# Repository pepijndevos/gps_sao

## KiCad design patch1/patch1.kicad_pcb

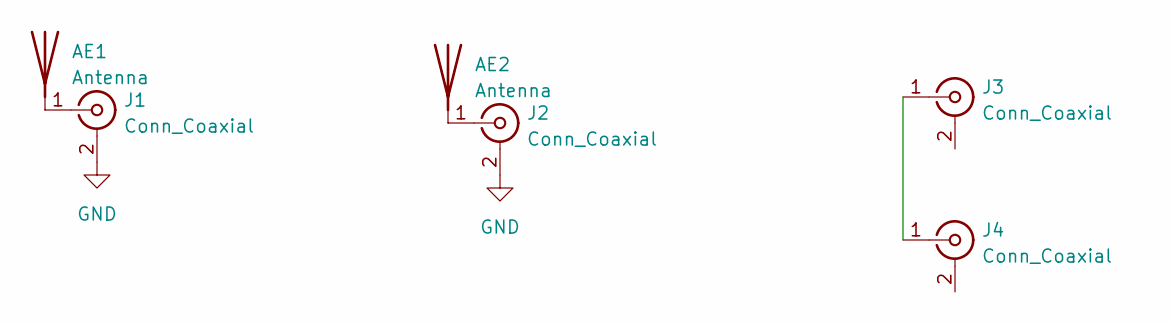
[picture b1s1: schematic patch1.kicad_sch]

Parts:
AE1: Antenna; patch_antenna_1.6ghz_cp
AE2: Antenna; patch_antenna_1.6ghz
J1, J2, J3, J4: Conn_Coaxial; coax

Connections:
GND: J1.2 (Ext), J2.2 (Ext)
unnamed: AE1.1 (A), J1.1 (In)
unnamed: AE2.1 (A), J2.1 (In)
unnamed: J3.1 (In), J4.1 (In)

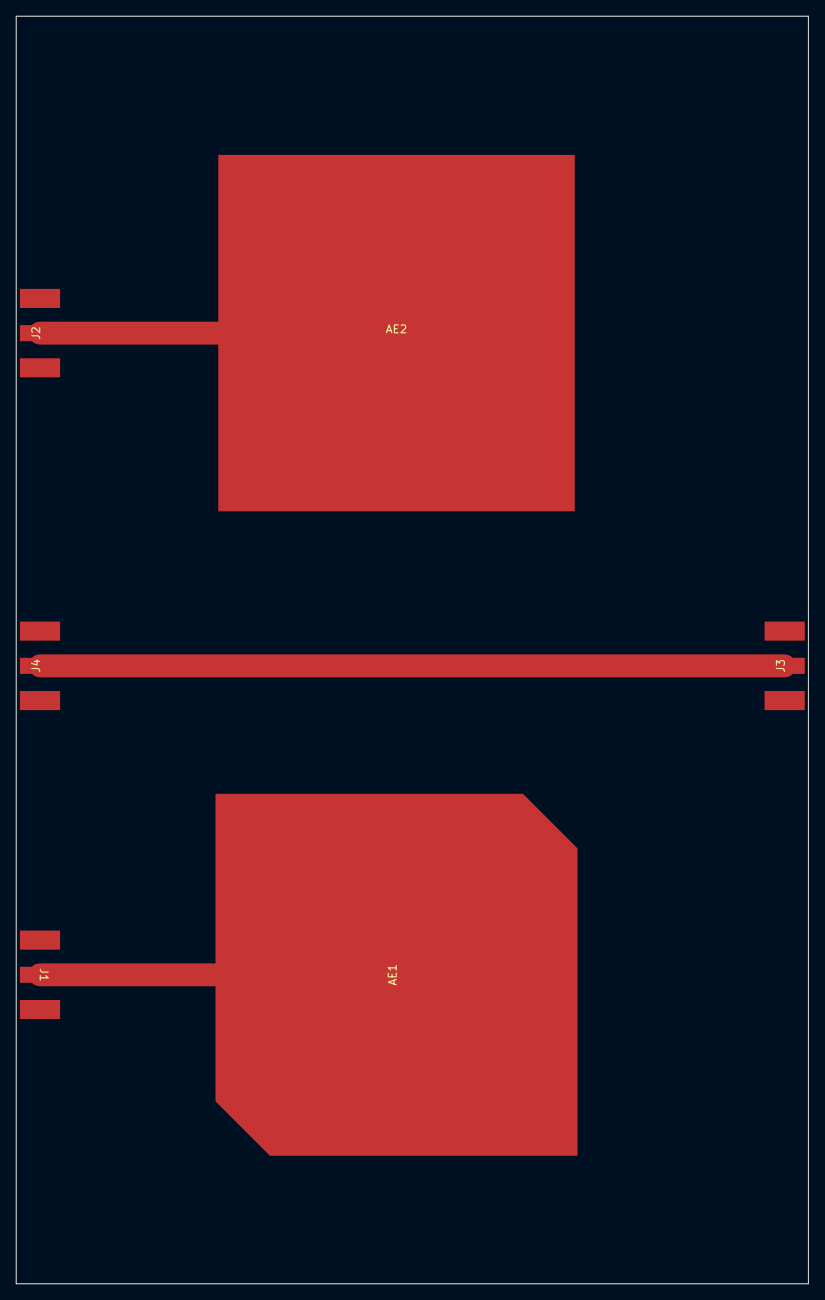
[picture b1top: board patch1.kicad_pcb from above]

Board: 2 copper layers, 100.0 x 160.0 mm, 6 parts (0 on the bottom side), 4 nets.

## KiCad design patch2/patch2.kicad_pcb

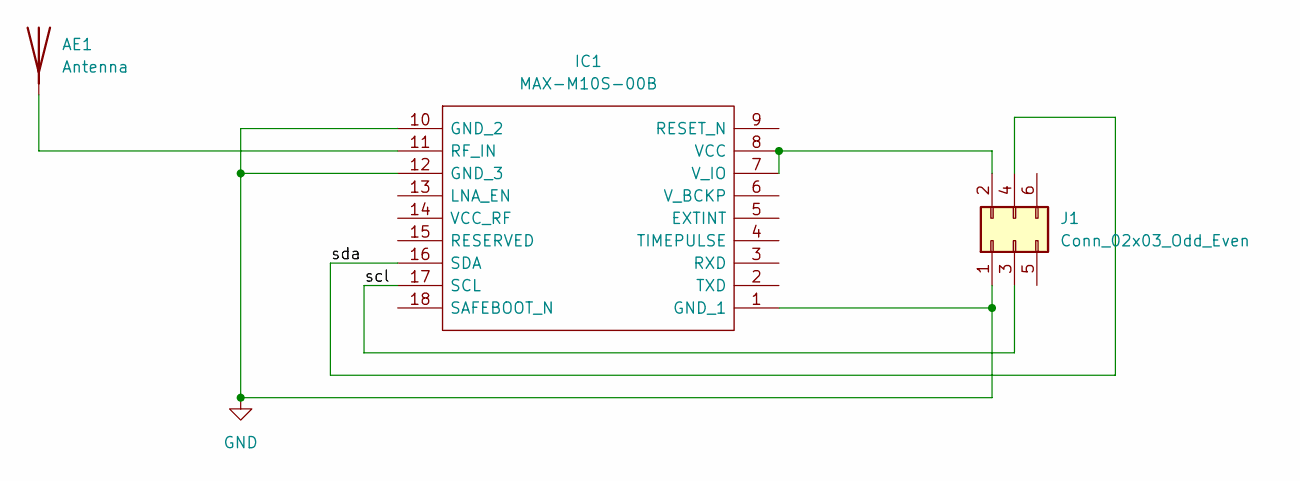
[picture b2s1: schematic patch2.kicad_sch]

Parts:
AE1: Antenna; patch_antenna_1.6ghz_cp
IC1: MAX-M10S-00B; MAXM10S00B; Mouser Part Number 377-MAX-M10S-00B
J1: Conn_02x03_Odd_Even

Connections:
/scl: IC1.17 (SCL), J1.3
/sda: IC1.16 (SDA), J1.4
GND: IC1.1 (GND_1), IC1.10 (GND_2), IC1.12 (GND_3), J1.1
unnamed: AE1.1 (A), IC1.11 (RF_IN)
unnamed: IC1.7 (V_IO), IC1.8 (VCC), J1.2

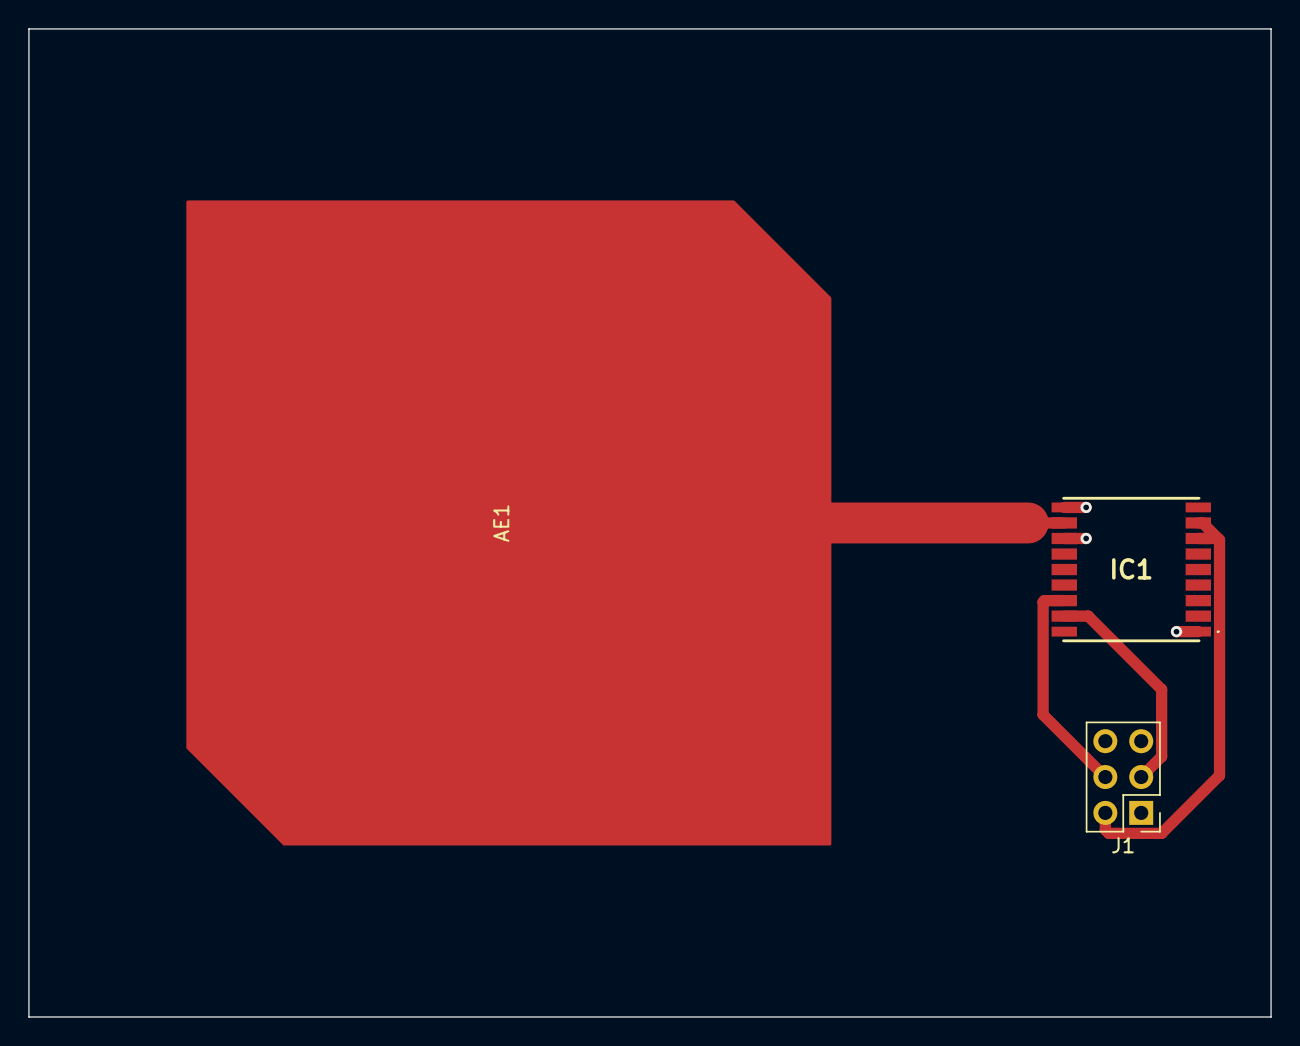
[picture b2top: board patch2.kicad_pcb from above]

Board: 2 copper layers, 88.0 x 70.0 mm, 3 parts (0 on the bottom side), 5 nets.

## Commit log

2022-11-24 add files
